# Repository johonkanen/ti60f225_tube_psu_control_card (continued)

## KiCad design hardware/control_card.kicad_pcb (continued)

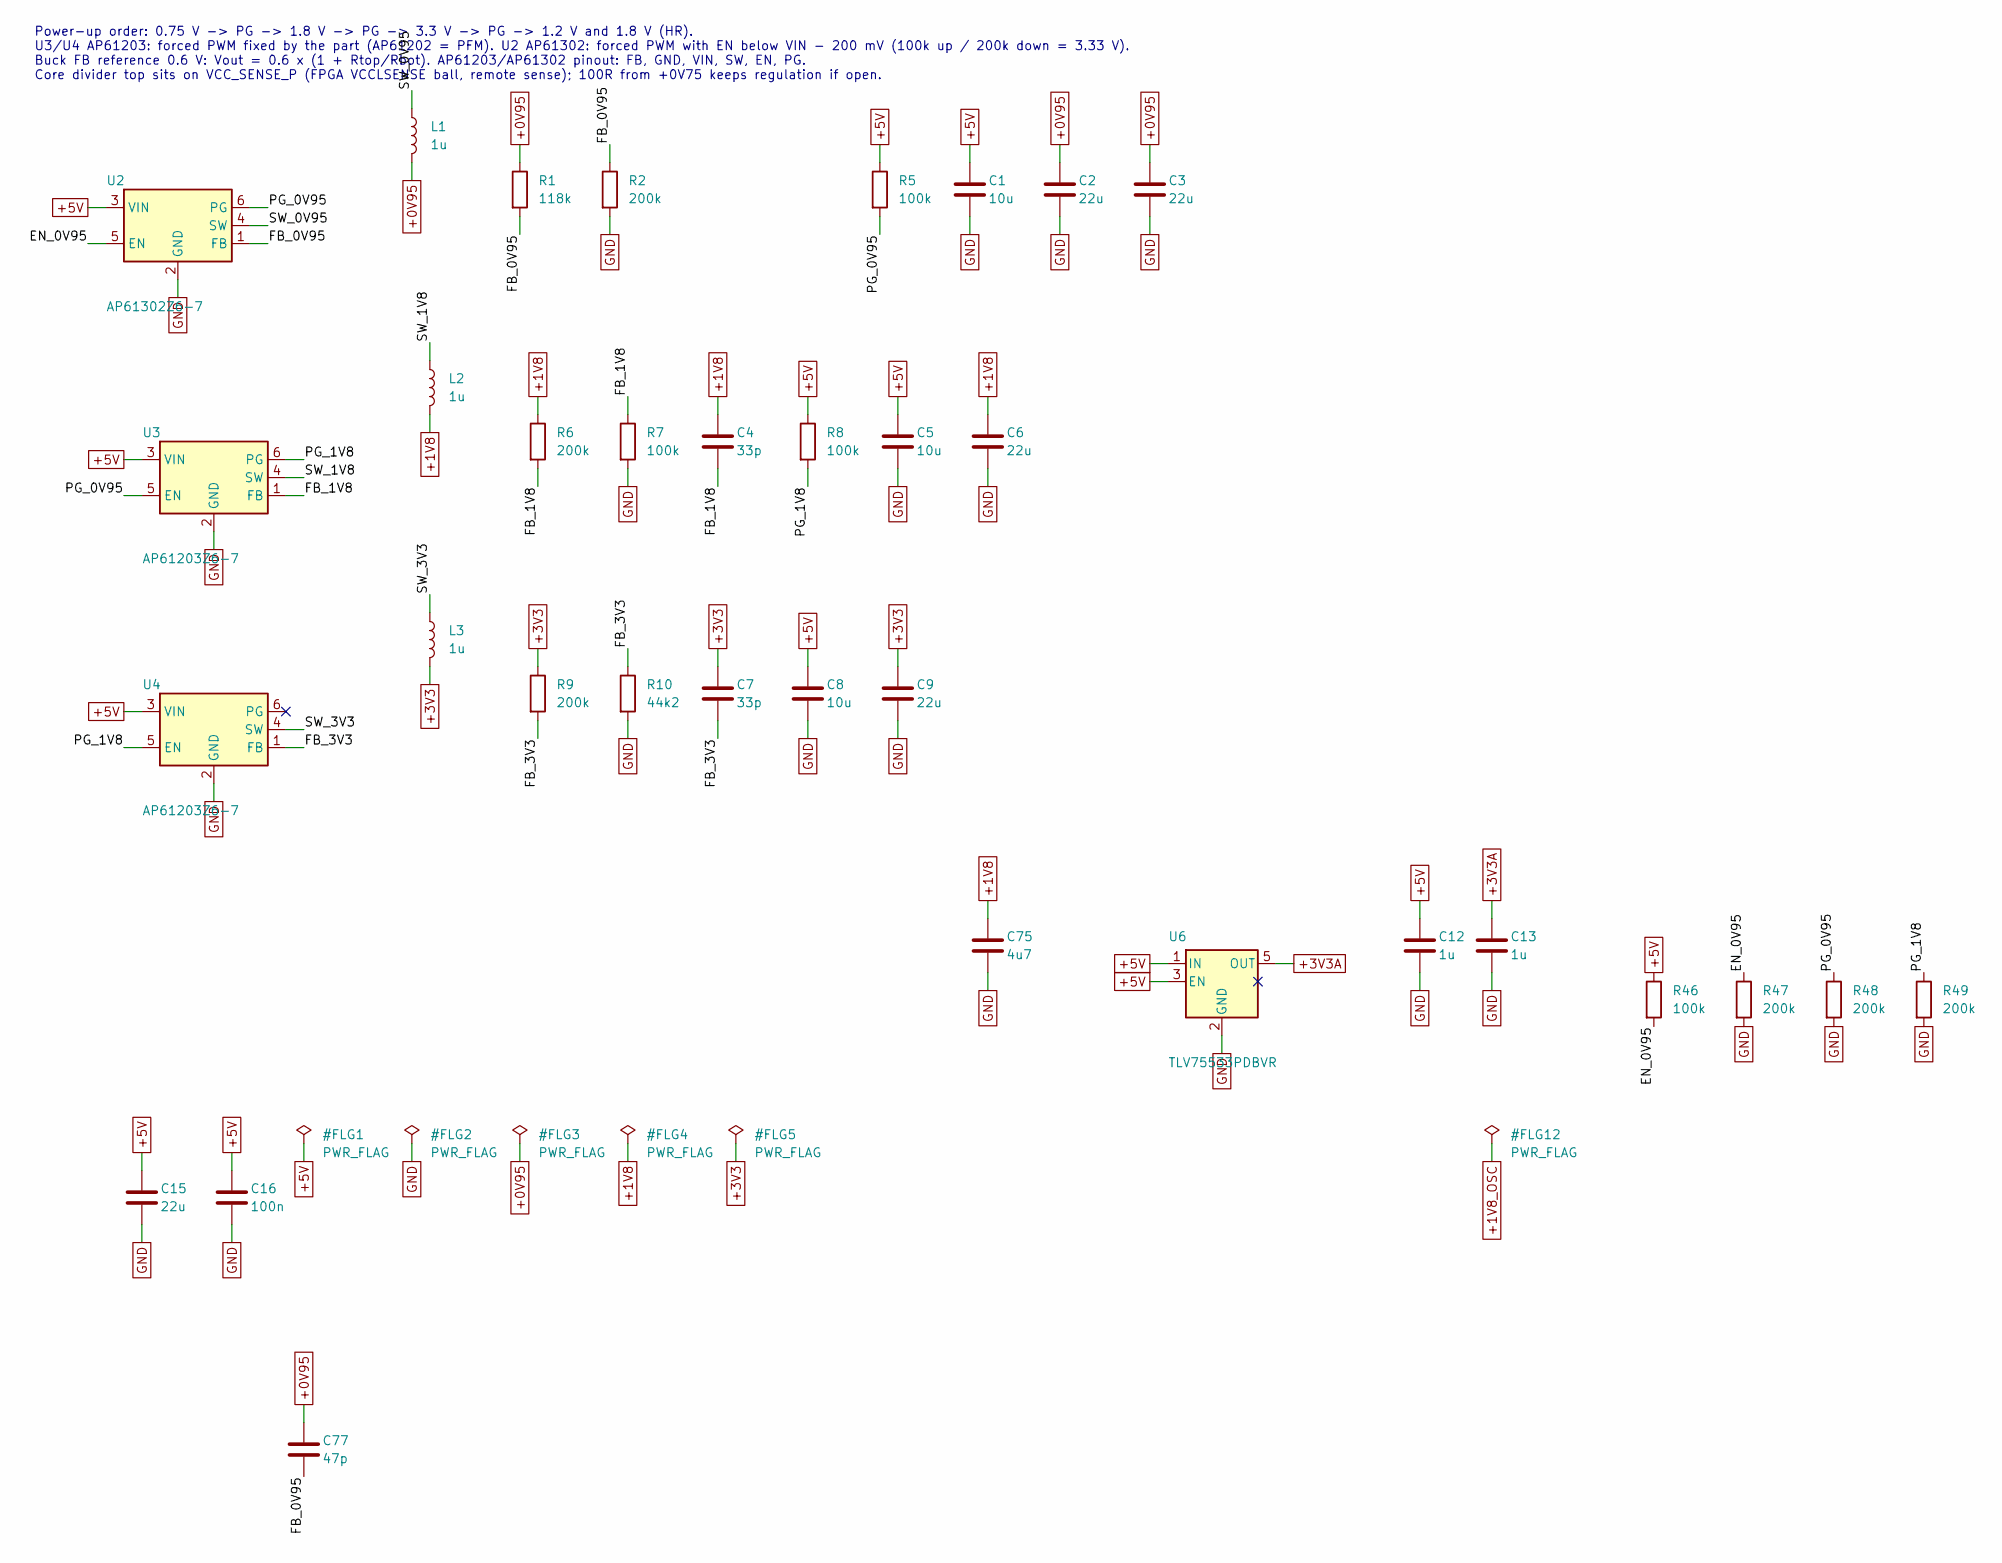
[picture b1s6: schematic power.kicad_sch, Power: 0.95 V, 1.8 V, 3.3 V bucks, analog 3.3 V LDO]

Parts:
C1, C5, C8: 10u; C_0603_1608Metric; MPN CL10A106KP8NNNC; LCSC C19702
C2, C3, C6, C9: 22u; C_0603_1608Metric; MPN CL10A226MQ8NRNC; LCSC C59461
C4, C7: 33p; C_0402_1005Metric; MPN 0402CG330J500NT; LCSC C1562
C12, C13: 1u; C_0402_1005Metric; MPN CL05A105KA5NQNC; LCSC C52923
C15: 22u; C_0805_2012Metric; MPN CL21A226MAQNNNE; LCSC C45783
C16: 100n; C_0402_1005Metric; MPN CL05B104KO5NNNC; LCSC C1525
C75: 4u7; C_0603_1608Metric; MPN CL10A475KO8NNNC; LCSC C19666
C77: 47p; C_0402_1005Metric; MPN 0402CG470J500NT; LCSC C1567
L1, L2, L3: 1u; L_Cenker_CKCS201610; MPN WPN201610H1R0MT; LCSC C97002
R1: 118k; R_0402_1005Metric; MPN 0402WGF1183TCE; LCSC C25748
R2, R6, R9, R47, R48, R49: 200k; R_0402_1005Metric; MPN 0402WGF2003TCE; LCSC C25764
R5, R7, R8: 100k; R_0402_1005Metric; MPN 0402WGF1003TCE; LCSC C25741
R10: 44k2; R_0402_1005Metric; MPN 0402WGF4422TCE; LCSC C25895
R46: 100k; R_0201_0603Metric; MPN RC0201FR-07100KL; LCSC C106224
U2: AP61302Z6-7; SOT-563; MPN AP61302Z6-7; LCSC C3193204
U3, U4: AP61203Z6-7; SOT-563; MPN AP61203Z6-7; LCSC C5244557
U6: TLV75533PDBVR; SOT-23-5; MPN TLV75533PDBVR; LCSC C404027

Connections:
+0V95: C2.1, C3.1, C77.1, L1.2, R1.1; also elsewhere on the board
+1V8: C4.1, C6.1, C75.1, L2.2, R6.1; also elsewhere on the board
+3V3: C7.1, C9.1, L3.2, R9.1; also elsewhere on the board
+3V3A: C13.1, U6.5 (OUT); also elsewhere on the board
+5V: C1.1, C5.1, C8.1, C12.1, C15.1, C16.1, R5.1, R8.1, R46.1, U2.3 (VIN), U3.3 (VIN), U4.3 (VIN), U6.1 (IN), U6.3 (EN); also elsewhere on the board
/Power/EN_0V95: R46.2, R47.1, U2.5 (EN)
/Power/FB_0V95: C77.2, R1.2, R2.1, U2.1 (FB)
/Power/FB_1V8: C4.2, R6.2, R7.1, U3.1 (FB)
/Power/FB_3V3: C7.2, R9.2, R10.1, U4.1 (FB)
/Power/PG_0V95: R5.2, R48.1, U2.6 (PG), U3.5 (EN)
/Power/PG_1V8: R8.2, R49.1, U3.6 (PG), U4.5 (EN)
/Power/SW_0V95: L1.1, U2.4 (SW)
/Power/SW_1V8: L2.1, U3.4 (SW)
/Power/SW_3V3: L3.1, U4.4 (SW)
GND: C1.2, C2.2, C3.2, C5.2, C6.2, C8.2, C9.2, C12.2, C13.2, C15.2, C16.2, C75.2, R2.2, R7.2, R10.2, R47.2, R48.2, R49.2, U2.2 (GND), U3.2 (GND), U4.2 (GND), U6.2 (GND); also elsewhere on the board

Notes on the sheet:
Power-up order: 0.75 V -> PG -> 1.8 V -> PG -> 3.3 V -> PG -> 1.2 V and 1.8 V (HR). U3/U4 AP61203: forced PWM fixed by the part (AP61202 = PFM). U2 AP61302: forced PWM with EN below VIN - 200 mV (100k up / 200k down = 3.33 V). Buck FB reference 0.6 V: Vout = 0.6 x (1 + Rtop/Rbot). AP61203/AP61302 p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

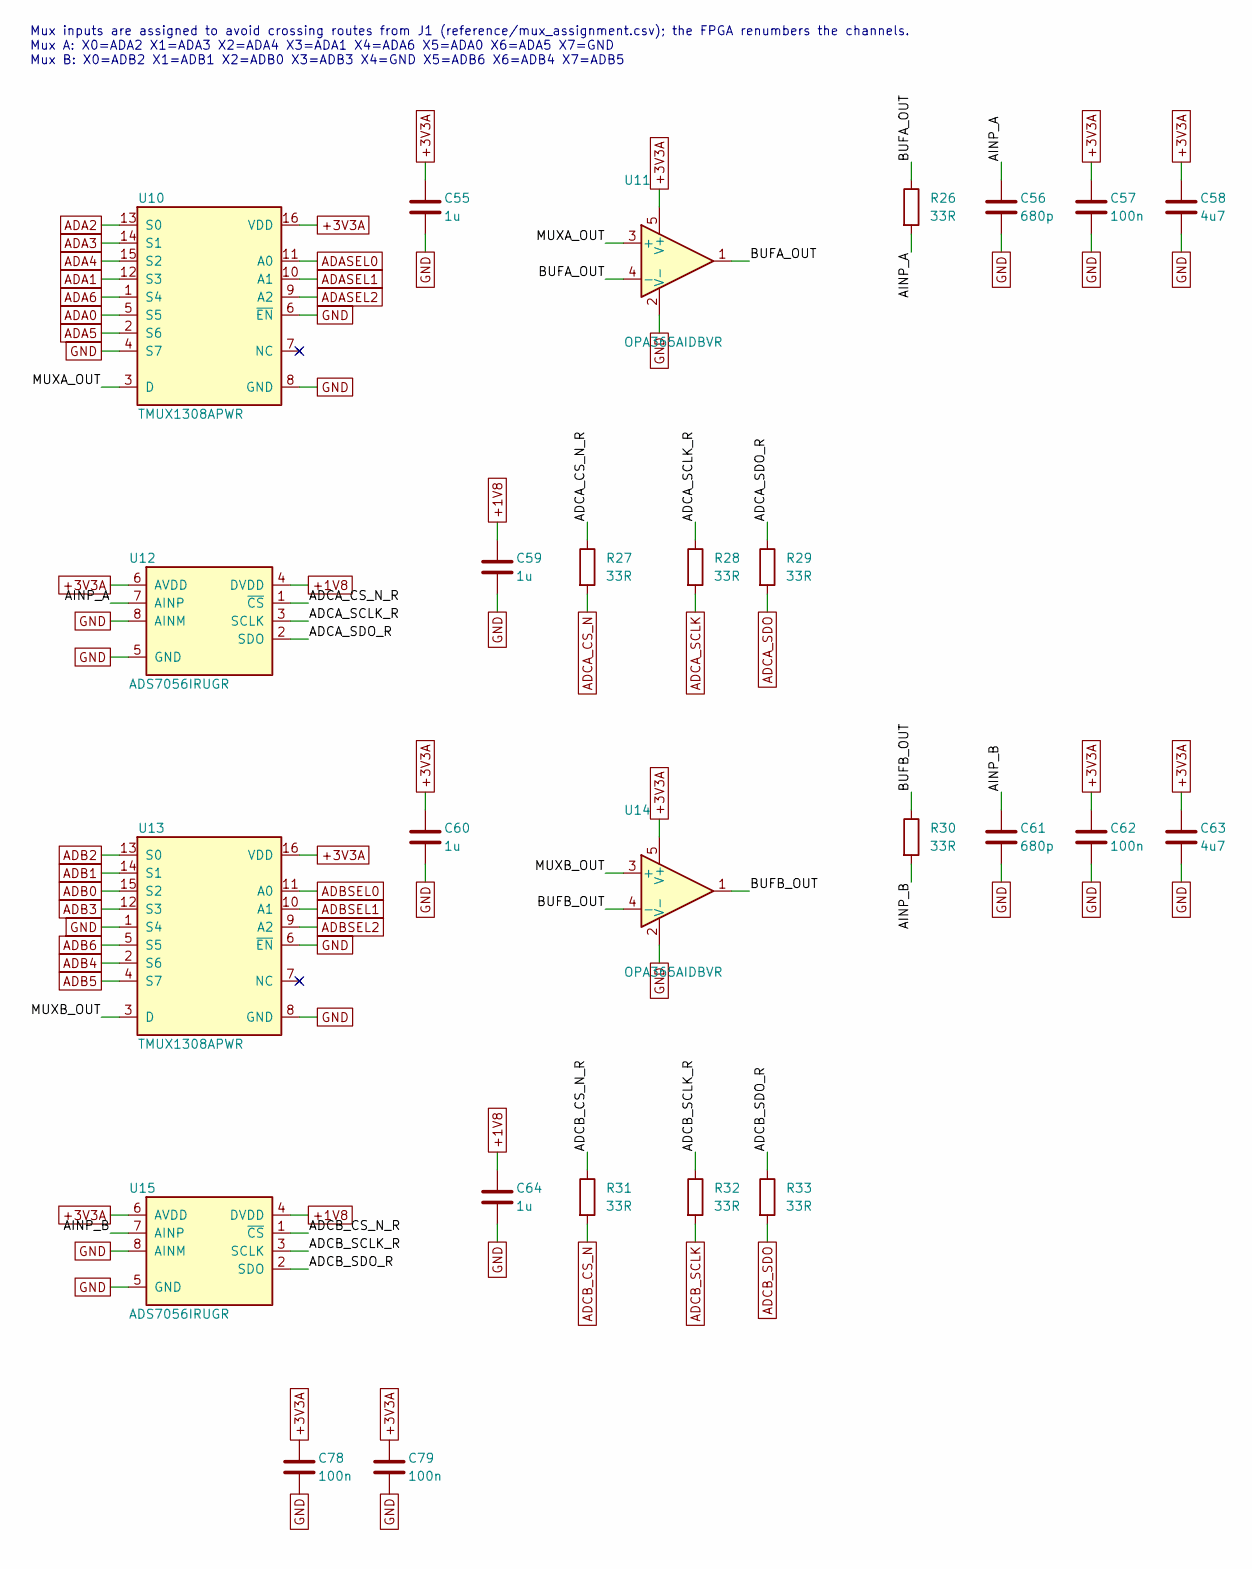
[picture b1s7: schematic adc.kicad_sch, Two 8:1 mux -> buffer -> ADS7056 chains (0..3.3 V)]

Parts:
C55, C59, C60, C64: 1u; C_0402_1005Metric; MPN CL05A105KA5NQNC; LCSC C52923
C56, C61: 680p; C_0402_1005Metric; MPN CC0402JRNPO9BN681; LCSC C113781
C57, C62, C78, C79: 100n; C_0402_1005Metric; MPN CL05B104KO5NNNC; LCSC C1525
C58, C63: 4u7; C_0603_1608Metric; MPN CL10A475KO8NNNC; LCSC C19666
R26, R30: 33R; R_0402_1005Metric; MPN 0402WGF330JTCE; LCSC C25105
R27, R28, R29, R32, R33: 33R; R_0201_0603Metric; MPN RC-01W33R0FT; LCSC C320843
R31: 33R; C_0201_0603Metric; MPN RC-01W33R0FT; LCSC C320843
U10, U13: TMUX1308APWR; TSSOP-16_4.4x5mm_P0.65mm; MPN TMUX1308APWR; LCSC C39707757
U11, U14: OPA365AIDBVR; SOT-23-5; MPN OPA365AIDBVR; LCSC C96626
U12, U15: ADS7056IRUGR; Texas_UQFN-8_1.5x1.5mm_P0.5mm; MPN ADS7056IRUGR; LCSC C2669798

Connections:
+1V8: C59.1, C64.1, U12.4 (DVDD), U15.4 (DVDD); also elsewhere on the board
+3V3A: C55.1, C57.1, C58.1, C60.1, C62.1, C63.1, C78.1, C79.1, U10.16 (VCC), U11.5 (V+), U12.6 (AVDD), U13.16 (VCC), U14.5 (V+), U15.6 (AVDD); also elsewhere on the board
/ADC/ADCA_CS_N_R: R27.1, U12.1 (~CS)
/ADC/ADCA_SCLK_R: R28.1, U12.3 (SCLK)
/ADC/ADCA_SDO_R: R29.1, U12.2 (SDO)
/ADC/ADCB_CS_N_R: R31.1, U15.1 (~CS)
/ADC/ADCB_SCLK_R: R32.1, U15.3 (SCLK)
/ADC/ADCB_SDO_R: R33.1, U15.2 (SDO)
/ADC/AINP_A: C56.1, R26.2, U12.7 (AINP)
/ADC/AINP_B: C61.1, R30.2, U15.7 (AINP)
/ADC/BUFA_OUT: R26.1, U11.1, U11.4 (-)
/ADC/BUFB_OUT: R30.1, U14.1, U14.4 (-)
/ADC/MUXA_OUT: U10.3 (A), U11.3 (+)
/ADC/MUXB_OUT: U13.3 (A), U14.3 (+)
ADA0: U10.5 (A5); also elsewhere on the board
ADA1: U10.12 (A3); also elsewhere on the board
ADA2: U10.13 (A0); also elsewhere on the board
ADA3: U10.14 (A1); also elsewhere on the board
ADA4: U10.15 (A2); also elsewhere on the board
ADA5: U10.2 (A6); also elsewhere on the board
ADA6: U10.1 (A4); also elsewhere on the board
ADASEL0: U10.11 (S0); also elsewhere on the board
ADASEL1: U10.10 (S1); also elsewhere on the board
ADASEL2: U10.9 (S2); also elsewhere on the board
ADB0: U13.15 (A2); also elsewhere on the board
ADB1: U13.14 (A1); also elsewhere on the board
ADB2: U13.13 (A0); also elsewhere on the board
ADB3: U13.12 (A3); also elsewhere on the board
ADB4: U13.2 (A6); also elsewhere on the board
ADB5: U13.4 (A7); also elsewhere on the board
ADB6: U13.5 (A5); also elsewhere on the board
ADBSEL0: U13.11 (S0); also elsewhere on the board
ADBSEL1: U13.10 (S1); also elsewhere on the board
ADBSEL2: U13.9 (S2); also elsewhere on the board
ADCA_CS_N: R27.2; also elsewhere on the board
ADCA_SCLK: R28.2; also elsewhere on the board
ADCA_SDO: R29.2; also elsewhere on the board
ADCB_CS_N: R31.2; also elsewhere on the board
ADCB_SCLK: R32.2; also elsewhere on the board
ADCB_SDO: R33.2; also elsewhere on the board
GND: C55.2, C56.2, C57.2, C58.2, C59.2, C60.2, C61.2, C62.2, C63.2, C64.2, C78.2, C79.2, U10.4 (A7), U10.6 (~E), U10.8 (GND), U11.2 (V-), U12.5 (GND), U12.8 (AINM), U13.1 (A4), U13.6 (~E), U13.8 (GND), U14.2 (V-), U15.5 (GND), U15.8 (AINM); also elsewhere on the board

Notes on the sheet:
Mux inputs are assigned to avoid crossing routes from J1 (reference/mux_assignment.csv); the FPGA renumbers the channels. Mux A: X0=ADA2 X1=ADA3 X2=ADA4 X3=ADA1 X4=ADA6 X5=ADA0 X6=ADA5 X7=GND Mux B: X0=ADB2 X1=ADB1 X2=ADB0 X3=ADB3 X4=GND X5=ADB6 X6=ADB4 X7=ADB5

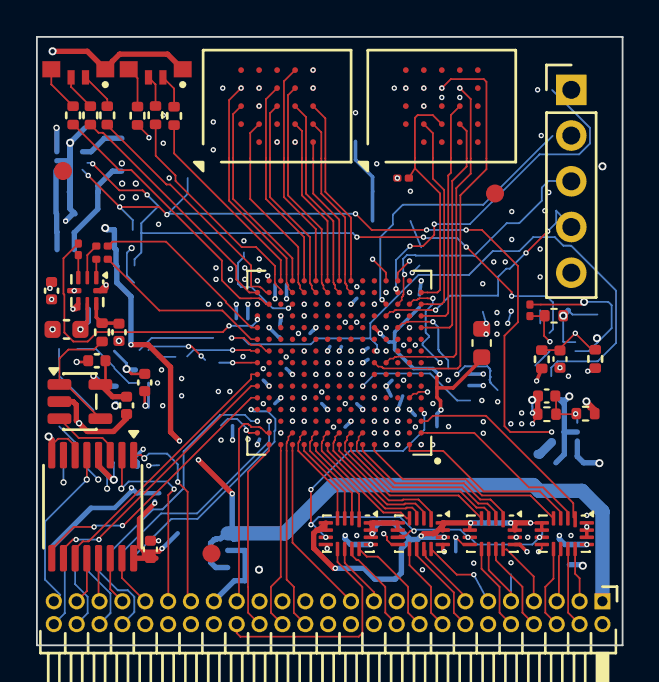
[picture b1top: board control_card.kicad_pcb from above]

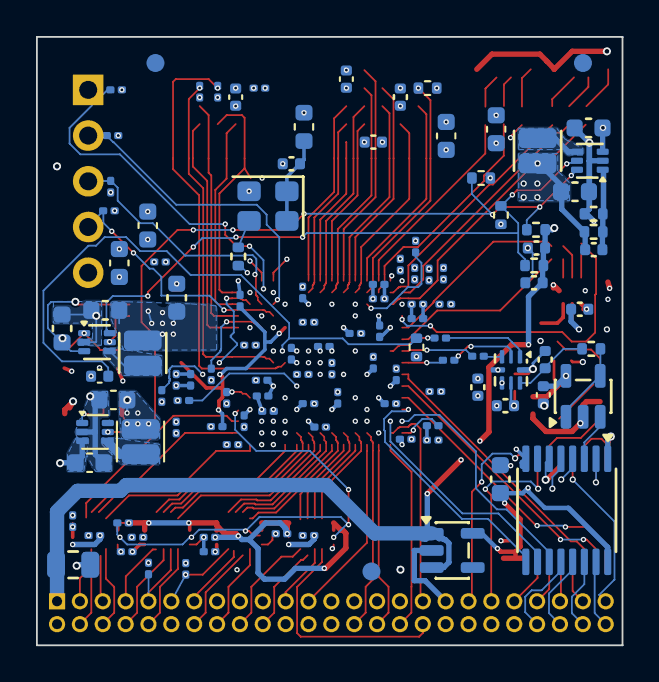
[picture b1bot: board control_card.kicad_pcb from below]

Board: 6 copper layers, 32.5 x 33.8 mm, 161 parts (117 on the bottom side), 148 nets.

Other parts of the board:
FID1, FID2, FID3, FID4, FID5, FID6: Fiducial; Fiducial_1mm_Mask2mm

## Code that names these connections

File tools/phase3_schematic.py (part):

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
# HyperRAM: the AC PSU card's pin map for the user's controller (bank 1B).
HYPERRAM = {
    "HR_CK": "GPIOL_N_16", "HR_CS_N": "GPIOL_P_18", "HR_DQ0": "GPIOL_P_14", "HR_DQ1": "GPIOL_N_09",
    "HR_DQ2": "GPIOL_N_17", "HR_DQ3": "GPIOL_N_15", "HR_DQ4": "GPIOL_P_16", "HR_DQ5": "GPIOL_N_14",
    "HR_DQ6": "GPIOL_N_10", "HR_DQ7": "GPIOL_P_10", "HR_RESET_N": "GPIOL_P_17", "HR_RWDS": "GPIOL_P_15",
}

# Header outputs through the translators, in J1 pin order (4 per SN74AVC4T774).
XLAT = [["PRI_DHB_HI", "EPWM6A", "PRI_DHB_LO", "EPWM5A"],
        ["CUK_CS", "HT_CS", "EPWM2A", "SYNCH_2"],
        ["EPWM2B", "CUK_CLK", "SYNCH_1", "HT_CLK"],
        ["GPIO_BYPASS_RLY", "PFC_PWM1", "EPWM1A", "PFC_PWM2"]]


def fpga_assignment():
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    cfg = {ball("CRESET_N"): "CRESET_N", ball("CDONE"): "CDONE", ball("TCK"): "TCK", ball("TMS"): "TMS",
           ball("TDI"): "TDI", ball("TDO"): "TDO",
           ball("REF_RES_2A"): "REF_RES_2A", ball("REF_RES_3A"): "REF_RES_3A", ball("REF_RES_4A"): "REF_RES_4A",
           ball("GPIOL_P_01_SSL_N"): "FLASH_CS_N", ball("GPIOL_N_01_CCK"): "FLASH_CLK",
           ball("GPIOL_P_03_CDI0"): "FLASH_IO0", ball("GPIOL_N_03_CDI1"): "FLASH_IO1",
           ball("GPIOL_P_04_CDI2"): "FLASH_IO2", ball("GPIOL_N_04_CDI3"): "FLASH_IO3",
           ball("GPIOL_P_02_CSI"): "CSI", ball("GPIOL_P_00_PLLIN0"): "CLK100M"}
    for uname in ("CONFIG_JTAG", "HSIO_1A"):
        u = units[uname]
        place_unit(sh, flow, FPGA, "U1", u, unit_nets(fl, u, cfg), "Ti60F225C4", fpga_props)
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
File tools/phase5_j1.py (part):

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    pad (x, 127.52) -> 45 deg -> (x - 0.635, 126.885) -> north -> (x - 0.635, STUB_Y)

F.Cu for the nets that arrive on top (translator outputs, the south-west HVIO nets), In2.Cu for the direct nets that
arrive on L3. PFC_PWM2 (pin 34, far west of its translator) instead runs south of the second row and comes up
through both rows between pins 21/23 and 22/24, so it crosses none of the HVIO nets that drop onto pins 23-33.
Mode pulldowns: the EPWM2A/EPWM2B pull-downs R40/R41 sit on the bottom just north of J1 pins 9 and 11, the JTAG
pull-ups R60-R63 just west of their J2 pins: a B.Cu stub joins each to its (through-hole) pin, so they need no via.
"""
import sys
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L3_PINS = (12, 22, 24, 26)                               # second-row pins reached on In2.Cu
POCKET = ()                                                      # east-edge escapes, north to south
BALL = ()       # via in the ball pad: now made by tools/phase5_vias.py, before the decoupling is placed
# bottom-side resistors placed at a through-hole pin by tools/phase5_decaps.py: the EPWM2A/2B pull-downs at J1,
# the JTAG pull-ups at J2
PULLDOWNS = (("R40", "J1", 9), ("R41", "J1", 11), ("R60", "J2", 1), ("R62", "J2", 2), ("R61", "J2", 3),
             ("R63", "J2", 4), ("R25", "X1", 3))    # (and the oscillator's series resistor to its output pad)
LOOP_PIN, LOOP_GAP_PINS, LOOP_Y = 34, (22, 24), 128.22   # PFC_PWM2: south of row 2, up between pins 22 and 24
# J1_P17 comes down the east side on L3, CUK_SDATA (pin 15) from the west: pin 17 is reached between the two rows,
# from the first-row gap east of pin 15, so the two do not cross
BETWEEN_PIN, BETWEEN_PAST = 17, 15

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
